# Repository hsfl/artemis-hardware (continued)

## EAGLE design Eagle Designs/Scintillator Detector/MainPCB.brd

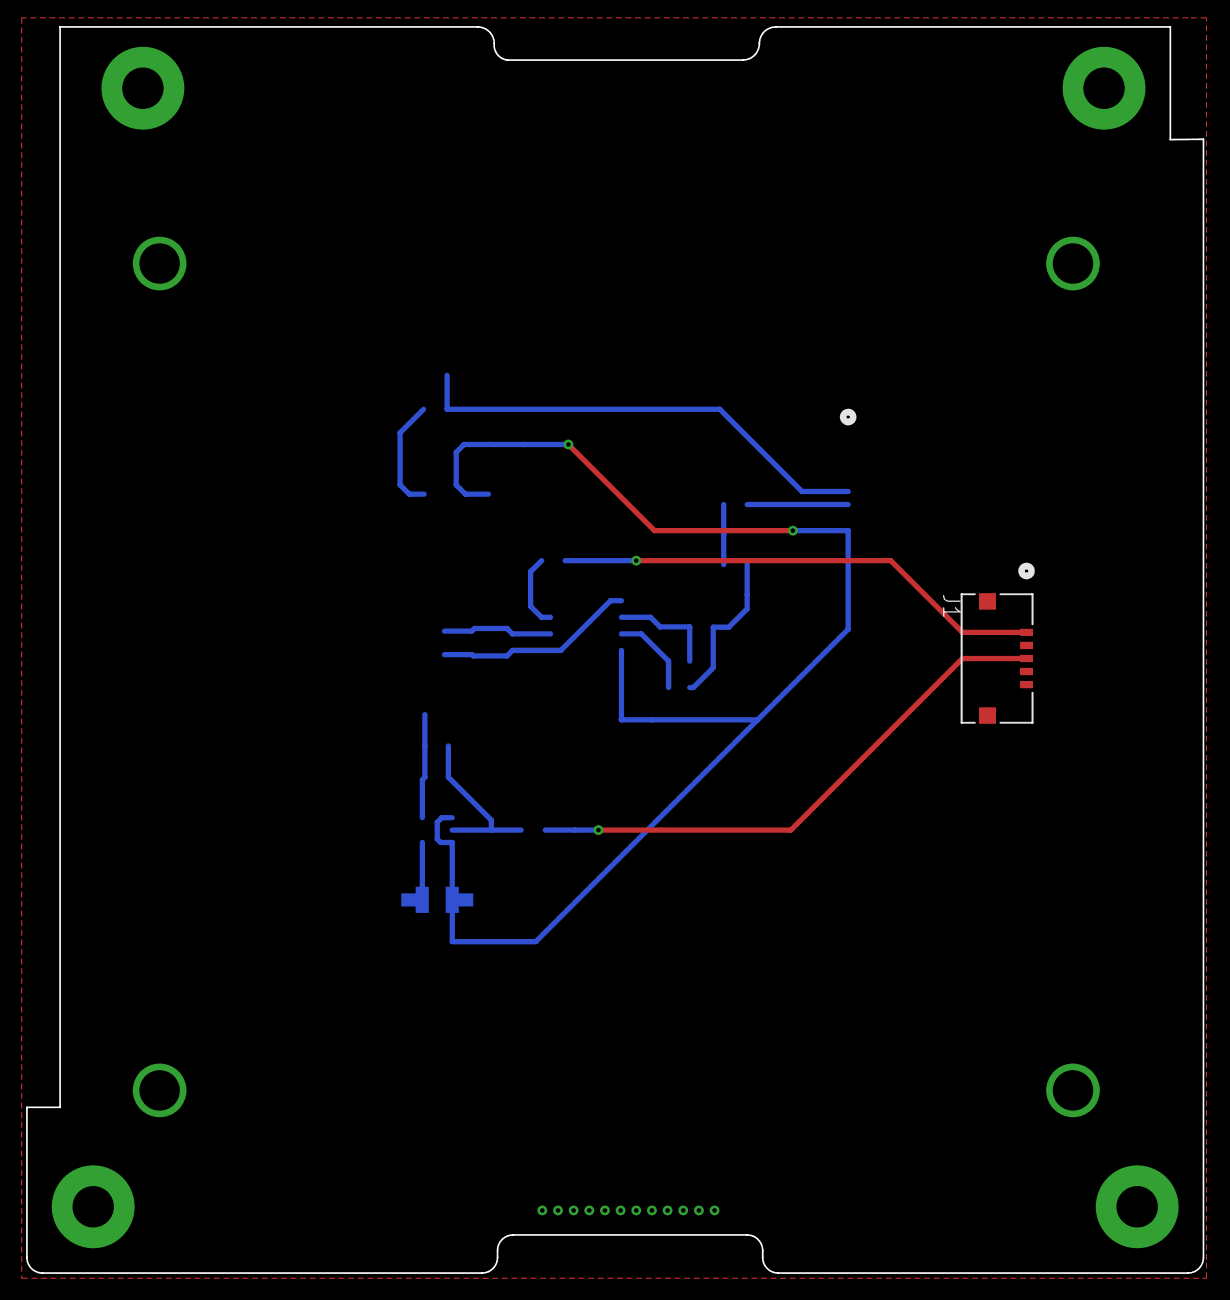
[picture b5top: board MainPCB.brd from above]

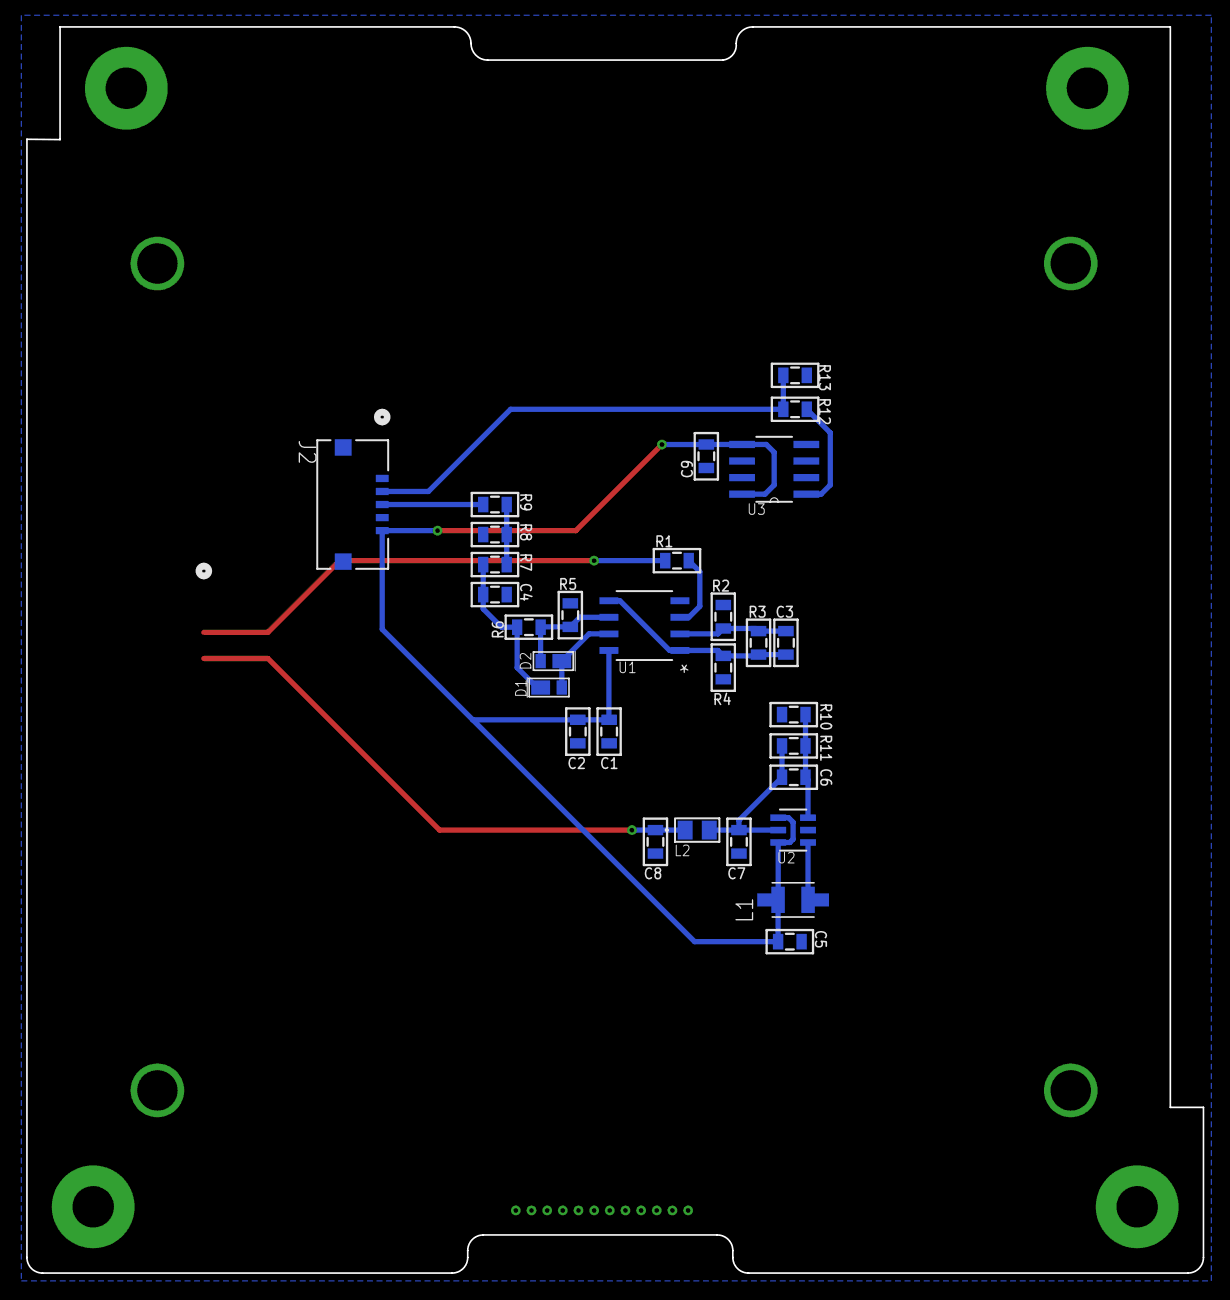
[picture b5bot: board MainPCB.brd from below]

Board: 2 copper layers, 90.2 x 95.5 mm, 32 parts (30 on the bottom side), 17 nets.

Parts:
C1: 10uF; 0805
C2, C9: 0.1uF; 0805
C3: 10pF; 0805
C4: 20nF; 0805
C5, C8: 1uF; 0805
C6: 22pF; 0805
C7: 0.47uF; 0805
D1, D2: RBR1VWM40ATR
J1, J2: 503763-0591; CONN_5037630591_MOL
L1: 47uH; IND_LQH32CN470K53L
L2: BK2125LM252-T; BK2125HS_TAY
R1: 1k; 0805
R2: 249; 0805
R3, R4, R10, R13: 10k; 0805
R5, R6: 100k; 0805
R7, R9: 0; 0805
R8: 24.9k; 0805
R11: 226k; 0805
R12: 45.3k; 0805
U1: LT1807IS8PBF; MSOP-8_MS_LIT
U2: LT3461AES6TRMPBF; TSOT-23_S6
U3: TMP36FSZ; SOIC127P600X175-8N
U$1: PC104_WCONN_DETECTOR

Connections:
5V: C1.2, C2.2, C5.2, C9.1, J2.5, L1.2, U1.8, U2.4, U2.6, U3.5, U3.8
GND: C1.1, C2.1, C4.2, C5.1, C7.2, C8.2, C9.2, J1.2, J1.4, J1.5, J1.6, J1.7, J2.1, J2.4, J2.6, J2.7, R2.1, R4.2, R5.1, R8.1, R10.1, R13.1, U1.4, U2.2, U3.4
unnamed: R1.2, U1.3
unnamed: C3.1, R2.2, R3.1, U1.2
unnamed: D2.+, R5.2, R6.1, U1.6
unnamed: C4.1, D1.-, R6.2, R7.1
unnamed: D1.+, D2.-, U1.7
unnamed: R7.2, R8.2, R9.1
unnamed: L1.1, U2.1
unnamed: C6.1, R10.2, R11.1, U2.3
unnamed: C6.2, C7.1, L2.2, R11.2, U2.5
unnamed: R12.2, U3.1
OUTA: C3.2, R3.2, R4.1, U1.1, U1.5
RASPI_SIG: J2.3, R9.2
SIPM_PWR: C8.1, J1.3, L2.1
SIPM_SIG: J1.1, R1.1
TMP_DATA: J2.2, R12.1, R13.2

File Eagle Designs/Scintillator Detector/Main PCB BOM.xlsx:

Part | Value | Device
C1 | 10uF | CAP0805
C2, C9 | 0.1uF | CAP0805
C3 | 10pF | CAP0805
C4 | 20nF | CAP0805
C5, C8 | 1uF | CAP0805
C6 | 22pF | CAP0805
C7 | 0.47uF | CAP0805
D1, D2 | RBR1VWM40ATR | RBR1VWM40ATR
J1, J2 | 503763-0591 | 503763-0591
L1 | 47uH | LQH32CN470K53L
L2 | BK2125LM252-T | BK2125LM252-T
R1 | 1k | RESISTOR0805-RES
R2 | 249 | RESISTOR0805-RES
R3, R4, R10, R13 | 10k | RESISTOR0805-RES
R5, R6 | 100k | RESISTOR0805-RES
R7, R9 | 0 | RESISTOR0805-RES
R8 | 24.9k | RESISTOR0805-RES
R11 | 226k | RESISTOR0805-RES
R12 | 45.3k | RESISTOR0805-RES
U1 | LT1807IS8PBF | LT1807IS8PBF
U2 | LT3461AES6TRMPBF | LT3461AES6TRMPBF
U3 | TMP36FSZ | TMP36FSZ
